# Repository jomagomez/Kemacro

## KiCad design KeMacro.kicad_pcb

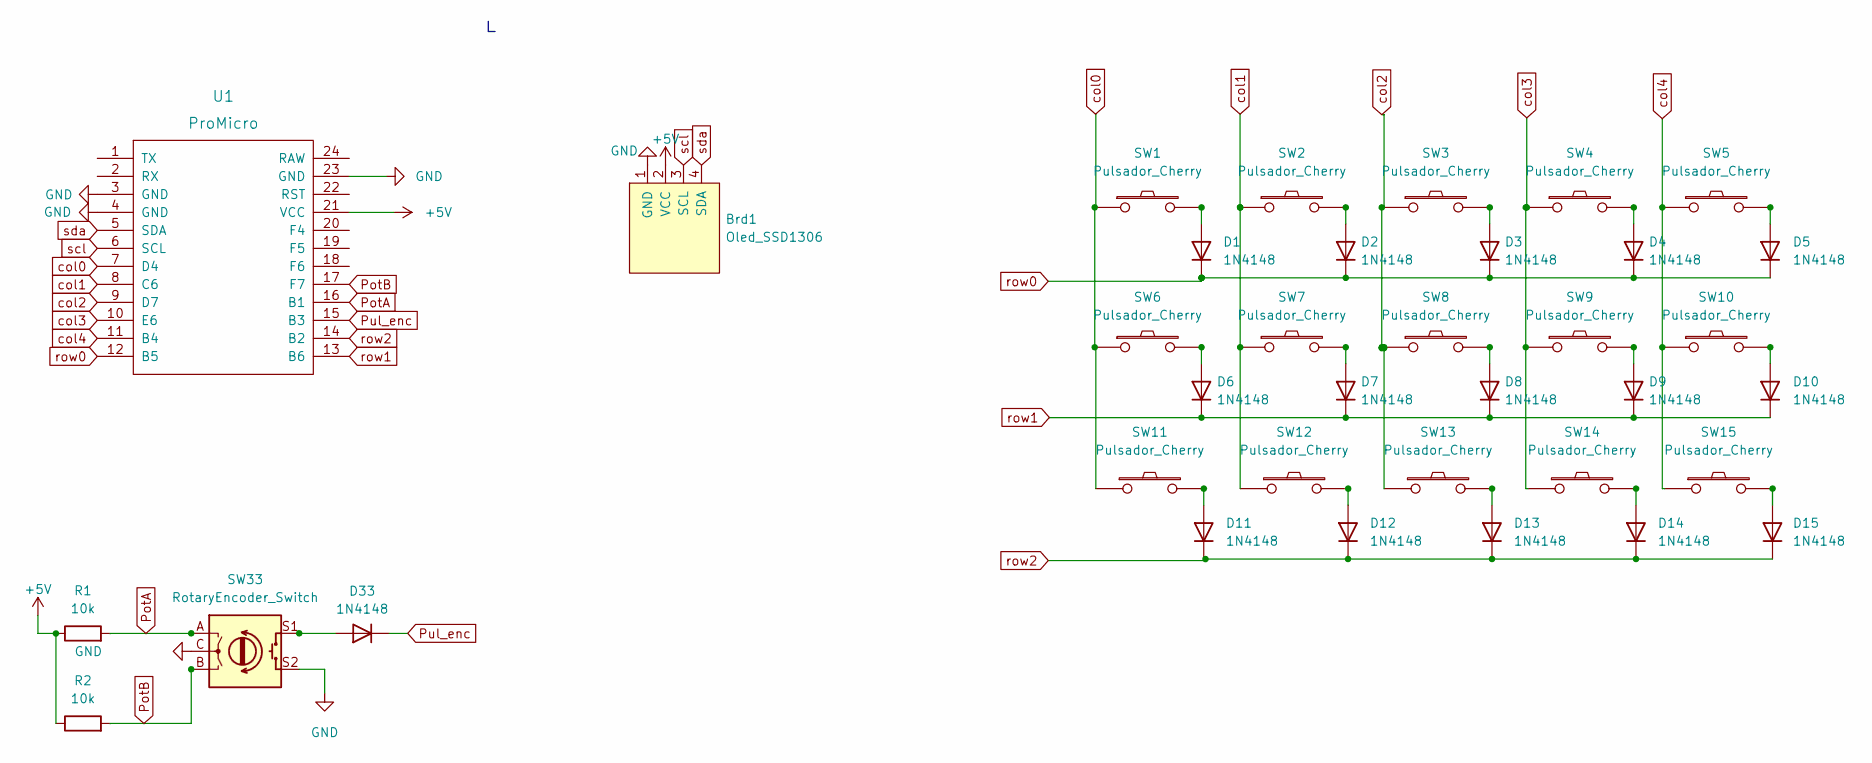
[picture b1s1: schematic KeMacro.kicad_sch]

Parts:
Brd1: Oled_SSD1306; OLED_SSD1306
D1, D2, D3, D4, D5, D6, D7, D8, D9, D10, D11, D12, D13, D14, D15, D33: 1N4148; D_DO-35_SOD27_P7.62mm_Horizontal
R1, R2: 10k; Resistencia
SW1, SW2, SW3, SW4, SW5, SW6, SW7, SW8, SW9, SW10, SW11, SW12, SW13, SW14, SW15: Pulsador_Cherry; SW_Cherry_MX_1.00u_PCB
SW33: RotaryEncoder_Switch; RotaryEncoder_Alps_EC11E-Switch_Vertical_H20mm
U1: ProMicro; Pro_Micro

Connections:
+5V: Brd1.2 (VCC), R1.1, R2.1, U1.21 (VCC)
GND: Brd1.1 (GND), SW33.C, SW33.S2, U1.3 (GND), U1.4 (GND), U1.23 (GND)
unnamed: D1.2 (A), SW1.2
unnamed: D2.2 (A), SW2.2
unnamed: D3.2 (A), SW3.2
unnamed: D4.2 (A), SW4.2
unnamed: D5.2 (A), SW5.2
unnamed: D6.2 (A), SW6.2
unnamed: D7.2 (A), SW7.2
unnamed: D8.2 (A), SW8.2
unnamed: D9.2 (A), SW9.2
unnamed: D10.2 (A), SW10.2
unnamed: D11.2 (A), SW11.2
unnamed: D12.2 (A), SW12.2
unnamed: D13.2 (A), SW13.2
unnamed: D14.2 (A), SW14.2
unnamed: D15.2 (A), SW15.2
unnamed: D33.2 (A), SW33.S1
PotA: R1.2, SW33.A, U1.16 (B1)
PotB: R2.2, SW33.B, U1.17 (F7)
Pul_enc: D33.1 (K), U1.15 (B3)
col0: SW1.1, SW6.1, SW11.1, U1.7 (D4)
col1: SW2.1, SW7.1, SW12.1, U1.8 (C6)
col2: SW3.1, SW8.1, SW13.1, U1.9 (D7)
col3: SW4.1, SW9.1, SW14.1, U1.10 (E6)
col4: SW5.1, SW10.1, SW15.1, U1.11 (B4)
row0: D1.1 (K), D2.1 (K), D3.1 (K), D4.1 (K), D5.1 (K), U1.12 (B5)
row1: D6.1 (K), D7.1 (K), D8.1 (K), D9.1 (K), D10.1 (K), U1.13 (B6)
row2: D11.1 (K), D12.1 (K), D13.1 (K), D14.1 (K), D15.1 (K), U1.14 (B2)
scl: Brd1.3 (SCL), U1.6 (SCL)
sda: Brd1.4 (SDA), U1.5 (SDA)

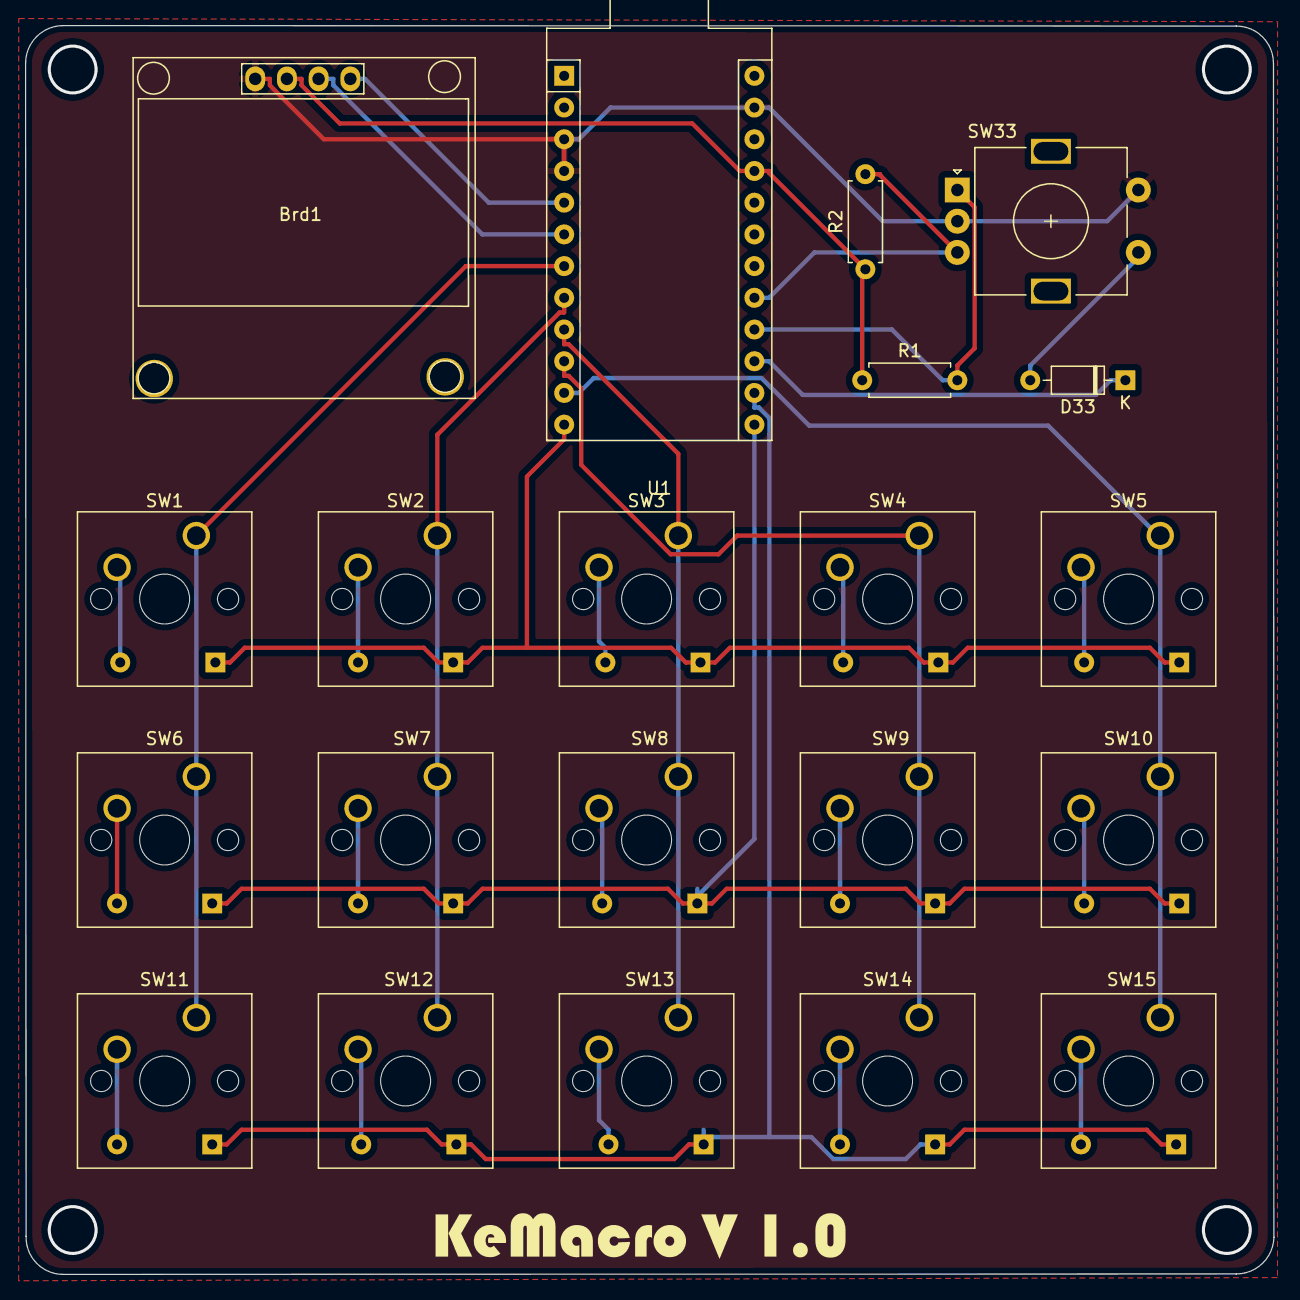
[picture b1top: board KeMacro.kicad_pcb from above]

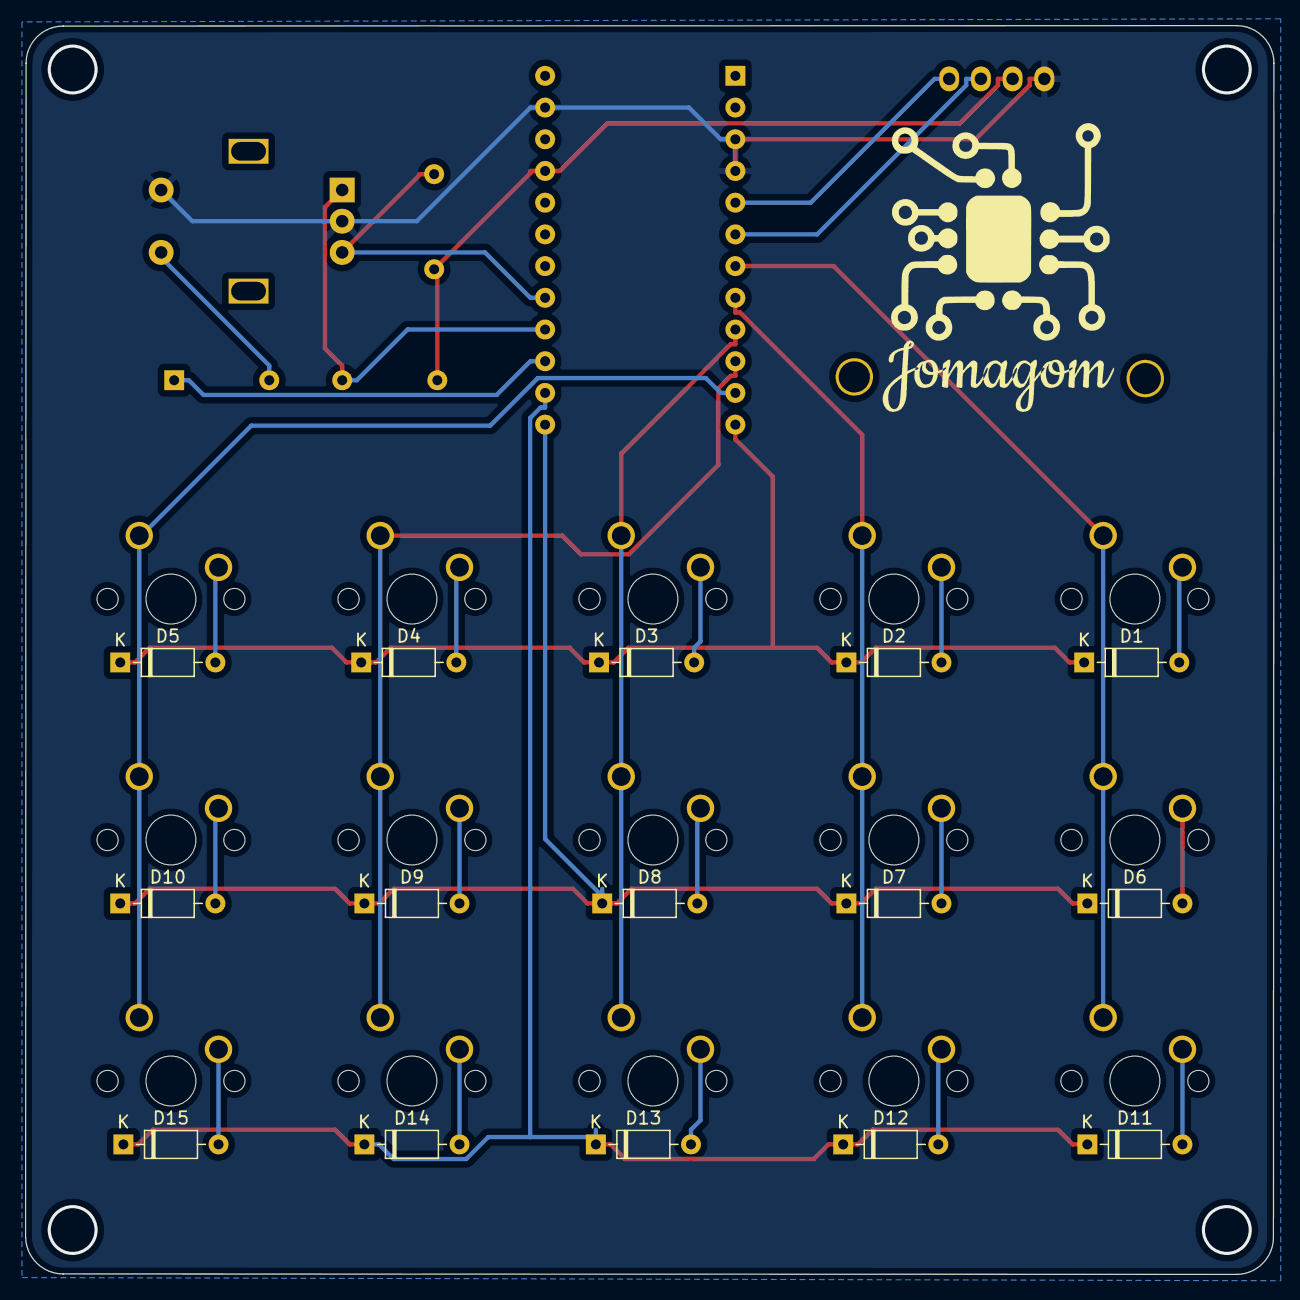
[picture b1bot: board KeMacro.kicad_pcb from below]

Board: 2 copper layers, 100.0 x 100.0 mm, 36 parts (15 on the bottom side), 31 nets.

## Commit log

2022-11-02 Se Agrega el proyecto
